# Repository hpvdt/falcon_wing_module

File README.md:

# falcon_wing_module
General purpose modules for handling wing duties

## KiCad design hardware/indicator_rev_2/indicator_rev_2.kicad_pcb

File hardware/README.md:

# Hardware Files

The designs for the wing module reside here. The module is an evolution of two separate boards on Falcon: the distributed voltage regulators (`servo_regulator`), and the spar load sensing boards (`spar_sensor`). As such, their design files are included in this repository for reference in addition to the actual wing module design files.

## Software Used

All designs were made in KiCad, version 9.0 as of writing.

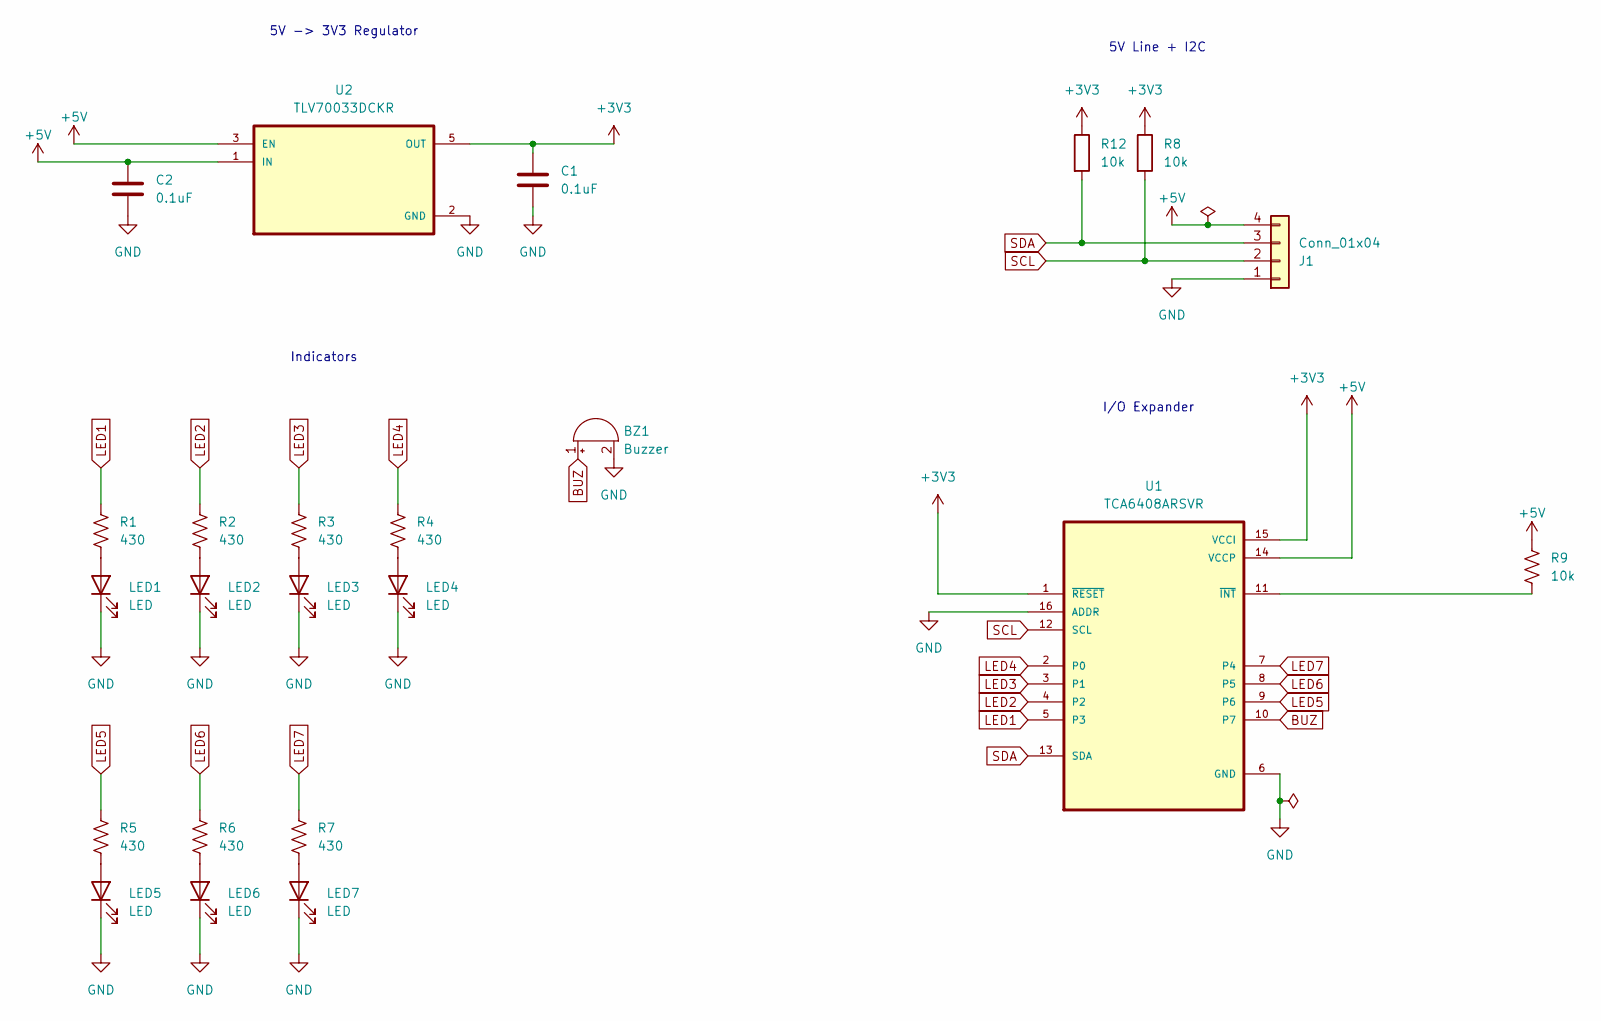
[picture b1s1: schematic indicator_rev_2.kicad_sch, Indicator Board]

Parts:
BZ1: Buzzer; Buzzer_12x9.5RM7.6
C1, C2: 0.1uF; C_0603_1608Metric
J1: Conn_01x04; JST_XH_S4B-XH-A_1x04_P2.50mm_Horizontal
LED1, LED2, LED3, LED4, LED5, LED6, LED7: LED; LED_D4.0mm
R1, R2, R3, R4, R5, R6, R7: 430; R_0603_1608Metric
R8, R9, R12: 10k; R_0603_1608Metric
U1: TCA6408ARSVR; QFN40P180X260X55-16N
U2: TLV70033DCKR; SOT65P210X110-5N

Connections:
+3V3: C1.1, R8.1, R12.1, U1.1 (~RESET), U1.15 (VCCI), U2.5 (OUT)
+5V: C2.1, J1.4, R9.2, U1.14 (VCCP), U2.1 (IN), U2.3 (EN)
BUZ: BZ1.1 (-), U1.10 (P7)
GND: BZ1.2 (+), C1.2, C2.2, J1.1, LED1.1 (K), LED2.1 (K), LED3.1 (K), LED4.1 (K), LED5.1 (K), LED6.1 (K), LED7.1 (K), U1.6 (GND), U1.16 (ADDR), U2.2 (GND)
LED1: R1.2, U1.5 (P3)
LED2: R2.2, U1.4 (P2)
LED3: R3.2, U1.3 (P1)
LED4: R4.2, U1.2 (P0)
LED5: R5.2, U1.9 (P6)
LED6: R6.2, U1.8 (P5)
LED7: R7.2, U1.7 (P4)
unnamed: LED1.2 (A), R1.1
unnamed: LED2.2 (A), R2.1
unnamed: LED3.2 (A), R3.1
unnamed: LED4.2 (A), R4.1
unnamed: LED5.2 (A), R5.1
unnamed: LED6.2 (A), R6.1
unnamed: LED7.2 (A), R7.1
unnamed: R9.1, U1.11 (~INT)
SCL: J1.2, R8.2, U1.12 (SCL)
SDA: J1.3, R12.2, U1.13 (SDA)

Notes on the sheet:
5V Line + I2C
I/O Expander
5V -> 3V3 Regulator
Indicators

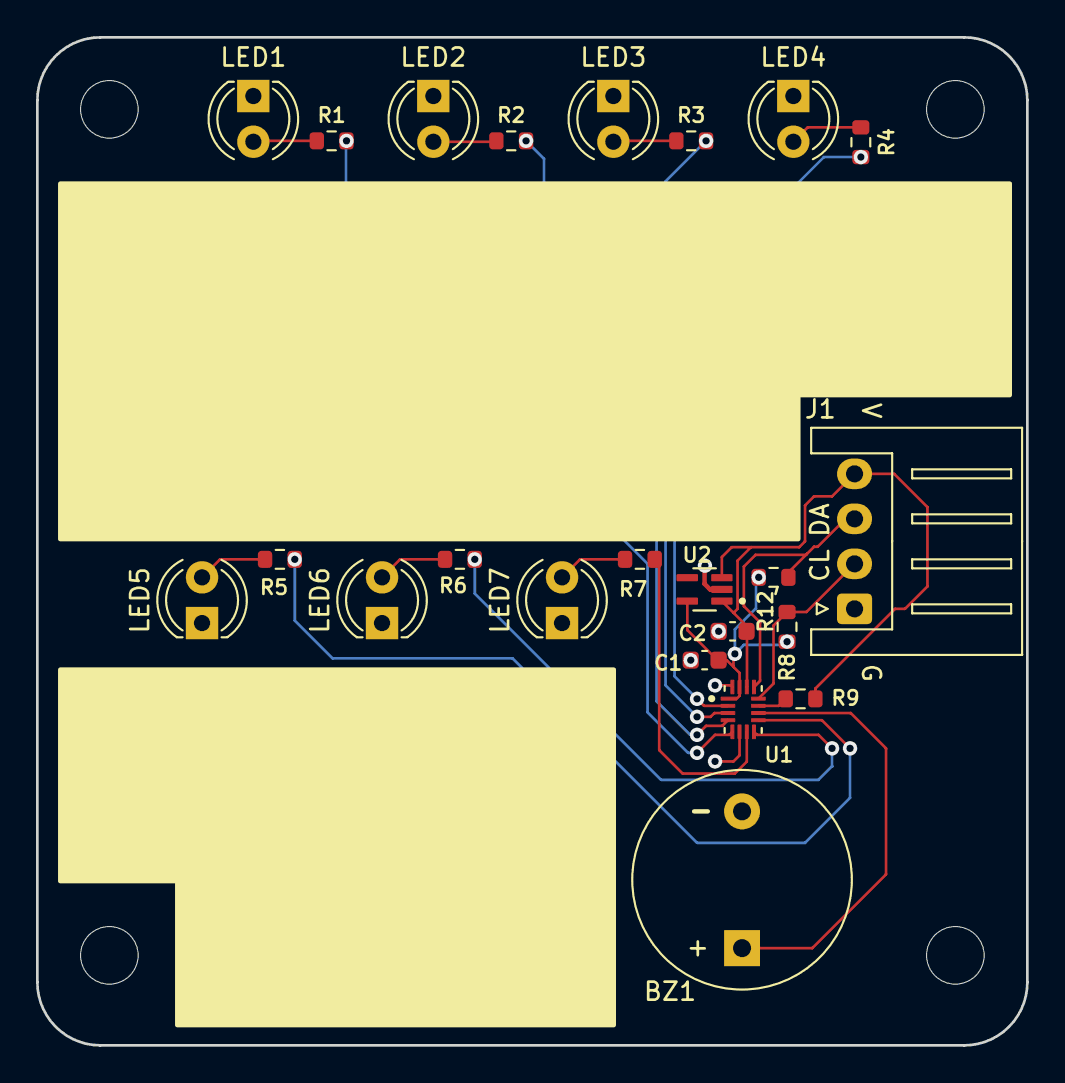
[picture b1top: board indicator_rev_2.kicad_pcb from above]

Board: 2 copper layers, 55.0 x 56.0 mm, 23 parts (0 on the bottom side), 21 nets.

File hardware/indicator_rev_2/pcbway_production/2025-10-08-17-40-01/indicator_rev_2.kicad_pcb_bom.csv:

Designator,Quantity,Value,Footprint,Package,MPN,DNP,Mount_Type,Description
BZ1,1,Buzzer,Buzzer_12x9.5RM7.6,"Plugin,D=12mm",KXG1203C,,tht,
"C1, C2",2,0.1uF,C_0603_1608Metric,0603,CL10B104KA8NNNC,,smt,Unpolarized capacitor
J1,1,Conn_01x04,JST_XH_S4B-XH-A_1x04_P2.50mm_Horizontal,"Push-Pull,P=2.5mm",S4B-XH-A(LF)(SN),,tht,"Generic connector, single row, 01x04, script generated (kicad-library-utils/schlib/autogen/connector/)"
"LED1, LED2, LED3, LED4, LED5, LED6, LED7",7,LED,LED_D4.0mm,"Plugin,D=4mm",TJ-L4FYTGCRMFCSFLC2R-A5,,tht,
"R1, R2, R3, R4, R5, R6, R7",7,430,R_0603_1608Metric,0603,0603WAF4300T5E,,smt,
"R12, R8, R9",3,10k,R_0603_1608Metric,0603,0603WAJ0103T5E,,smt,Resistor
U1,1,TCA6408ARSVR,QFN40P180X260X55-16N,UQFN-16(1.8x2.6),TCA6408ARSVR,,smt,
U2,1,TLV70033DCKR,SOT65P210X110-5N,SC-70-5,TLV70033DCKR,,smt,

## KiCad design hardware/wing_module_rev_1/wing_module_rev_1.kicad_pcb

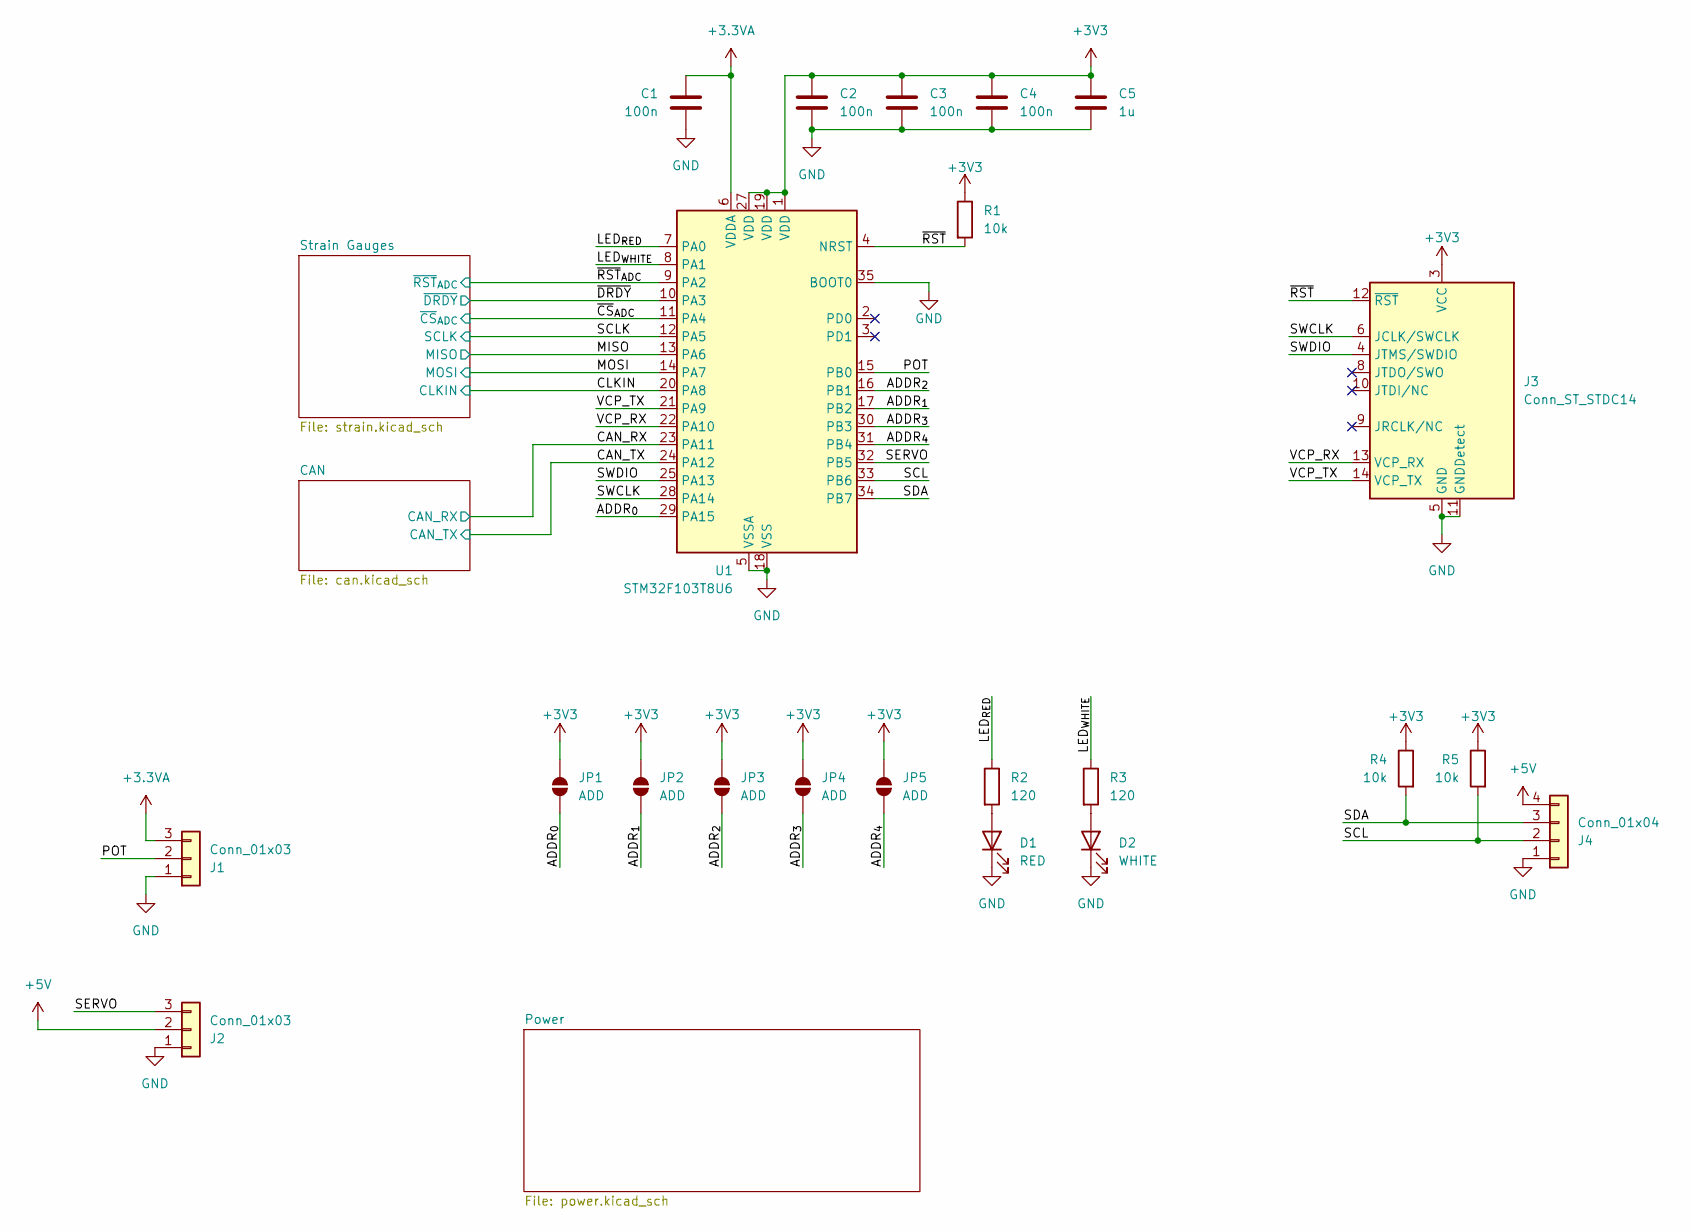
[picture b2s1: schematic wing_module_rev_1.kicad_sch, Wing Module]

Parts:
C1, C2, C3, C4: 100n; C_0402_1005Metric; LCSC C5448875
C5: 1u; C_0402_1005Metric; LCSC C52923
D1: RED; LED_0805_2012Metric; LCSC C84256
D2: WHITE; LED_0805_2012Metric; LCSC C34499
J1, J2: Conn_01x03; JST_EH_B3B-EH-A_1x03_P2.50mm_Vertical; LCSC C398546
J3: Conn_ST_STDC14; PinHeader_2x07_P1.27mm_Vertical_SMD; LCSC C6332251
J4: Conn_01x04; JST_EH_B4B-EH-A_1x04_P2.50mm_Vertical; LCSC C160258
JP1, JP2, JP3, JP4, JP5: ADD; SolderJumper-2_P1.3mm_Open_TrianglePad1.0x1.5mm; LCSC N/A
R1, R4, R5: 10k; R_0402_1005Metric; LCSC C723353
R2, R3: 120; R_0402_1005Metric; LCSC C25079
U1: STM32F103T8U6; QFN-36-1EP_6x6mm_P0.5mm_EP3.7x3.7mm; LCSC C19671

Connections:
+3.3VA: C1.1, J1.3, U1.6 (VDDA); also elsewhere on the board
+3V3: C2.1, C3.1, C4.1, C5.1, J3.3 (VCC), JP1.2 (B), JP2.2 (B), JP3.2 (B), JP4.2 (B), JP5.2 (B), R1.1, R4.1, R5.1, U1.1 (VDD), U1.19 (VDD), U1.27 (VDD); also elsewhere on the board
+5V: J2.2, J4.4; also elsewhere on the board
/ADDR_{0}: JP1.1 (A), U1.29 (PA15)
/ADDR_{1}: JP2.1 (A), U1.17 (PB2)
/ADDR_{2}: JP3.1 (A), U1.16 (PB1)
/ADDR_{3}: JP4.1 (A), U1.30 (PB3)
/ADDR_{4}: JP5.1 (A), U1.31 (PB4)
/CAN_RX: U1.23 (PA11); also elsewhere on the board
/CAN_TX: U1.24 (PA12); also elsewhere on the board
/CLKIN: U1.20 (PA8); also elsewhere on the board
/LED_{RED}: R2.1, U1.7 (PA0)
/LED_{WHITE}: R3.1, U1.8 (PA1)
/MISO: U1.13 (PA6); also elsewhere on the board
/MOSI: U1.14 (PA7); also elsewhere on the board
/POT: J1.2, U1.15 (PB0)
/SCL: J4.2, R5.2, U1.33 (PB6)
/SCLK: U1.12 (PA5); also elsewhere on the board
/SDA: J4.3, R4.2, U1.34 (PB7)
/SERVO: J2.3, U1.32 (PB5)
/SWCLK: J3.6 (JCLK/SWCLK), U1.28 (PA14)
/SWDIO: J3.4 (JTMS/SWDIO), U1.25 (PA13)
/VCP_RX: J3.13 (VCP_RX), U1.22 (PA10)
/VCP_TX: J3.14 (VCP_TX), U1.21 (PA9)
/~CS_{ADC}: U1.11 (PA4); also elsewhere on the board
/~DRDY: U1.10 (PA3); also elsewhere on the board
/~RST: J3.12 (~RST), R1.2, U1.4 (NRST)
/~RST_{ADC}: U1.9 (PA2); also elsewhere on the board
GND: C1.2, C2.2, C3.2, C4.2, C5.2, D1.1 (K), D2.1 (K), J1.1, J2.1, J3.5 (GND), J3.7 (GND), J3.11 (GNDDetect), J4.1, U1.5 (VSSA), U1.18 (VSS), U1.26 (VSS), U1.35 (BOOT0), U1.36 (VSS), U1.37 (VSS); also elsewhere on the board
unnamed: D1.2 (A), R2.2
unnamed: D2.2 (A), R3.2

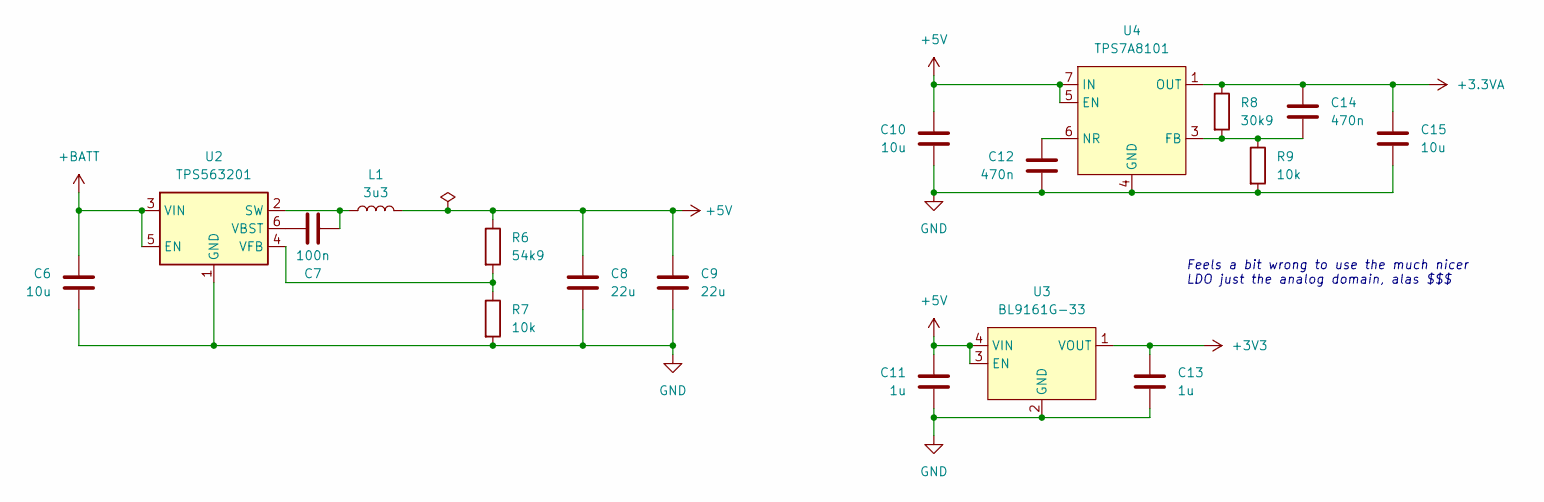
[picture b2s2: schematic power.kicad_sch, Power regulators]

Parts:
C6, C10, C15: 10u; C_0603_1608Metric; LCSC C5360828
C7: 100n; C_0402_1005Metric; LCSC C5448875
C8, C9: 22u; C_0603_1608Metric; LCSC C86295
C11, C13: 1u; C_0402_1005Metric; LCSC C52923
C12, C14: 470n; C_0402_1005Metric; LCSC C47339
L1: 3u3; L_Changjiang_FNR6045S; LCSC C168063
R6: 54k9; R_0402_1005Metric; LCSC C227137
R7, R9: 10k; R_0402_1005Metric; LCSC C723353
R8: 30k9; R_0402_1005Metric; LCSC C1883526
U2: TPS563201; SOT-23-6; LCSC C116592
U3: BL9161G-33; UDFN-4-1EP_1x1mm_P0.65mm_EP0.48x0.48mm; LCSC C2999146
U4: TPS7A8101; VSON-8-1EP_3x3mm_P0.65mm_EP1.65x2.4mm; LCSC C465730

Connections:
+3.3VA: C14.1, C15.1, R8.1, U4.1 (OUT), U4.2 (OUT); also elsewhere on the board
+3V3: C13.1, U3.1 (VOUT); also elsewhere on the board
+5V: C8.1, C9.1, C10.1, C11.1, L1.2, R6.1, U3.3 (EN), U3.4 (VIN), U4.5 (EN), U4.7 (IN), U4.8 (IN); also elsewhere on the board
+BATT: C6.1, U2.3 (VIN), U2.5 (EN); also elsewhere on the board
GND: C6.2, C8.2, C9.2, C10.2, C11.2, C12.2, C13.2, C15.2, R7.2, R9.2, U2.1 (GND), U3.2 (GND), U3.5 (GND), U4.4 (GND), U4.9 (GND); also elsewhere on the board
unnamed: C7.2, L1.1, U2.2 (SW)
unnamed: C7.1, U2.6 (VBST)
unnamed: R6.2, R7.1, U2.4 (VFB)
unnamed: C14.2, R8.2, R9.1, U4.3 (FB)
unnamed: C12.1, U4.6 (NR)

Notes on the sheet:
Feels a bit wrong to use the much nicer LDO just the analog domain, alas $$$

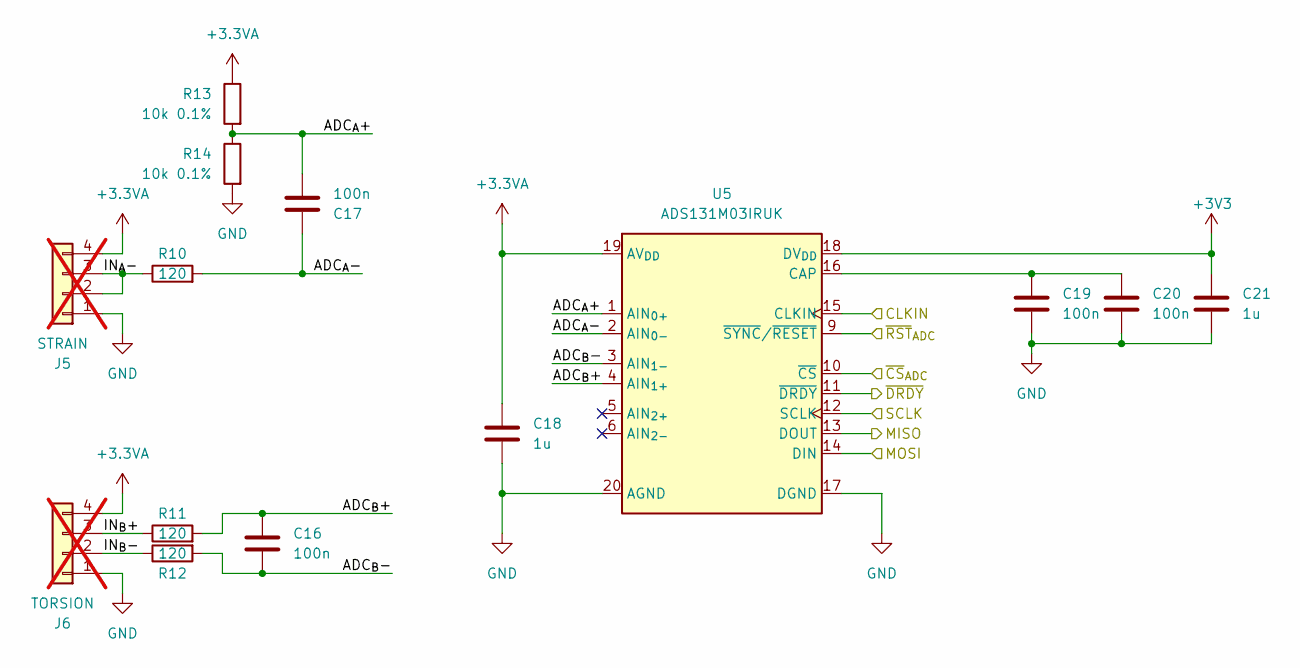
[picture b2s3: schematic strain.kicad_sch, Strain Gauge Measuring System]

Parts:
C16, C17, C19, C20: 100n; C_0402_1005Metric; LCSC C5448875
C18, C21: 1u; C_0402_1005Metric; LCSC C52923
J5: STRAIN; PinHeader_1x04_P2.00mm_Vertical; LCSC N/A; not fitted
J6: TORSION; PinHeader_1x04_P2.00mm_Vertical; LCSC N/A; not fitted
R10, R11, R12: 120; R_0402_1005Metric; LCSC C25079
R13, R14: 10k 0.1%; R_0402_1005Metric; LCSC C191915
U5: ADS131M03IRUK; WQFN-20-1EP_3x3mm_P0.4mm_EP1.7x1.7mm; LCSC C5116472

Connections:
+3.3VA: C18.1, J5.4, J6.4, R13.1, U5.19 (AV_{DD}); also elsewhere on the board
+3V3: C21.1, U5.18 (DV_{DD}); also elsewhere on the board
/CLKIN: U5.15 (CLKIN); also elsewhere on the board
/MISO: U5.13 (DOUT); also elsewhere on the board
/MOSI: U5.14 (DIN); also elsewhere on the board
/SCLK: U5.12 (SCLK); also elsewhere on the board
/Strain Gauges/ADC_{A}+: C17.2, R13.2, R14.1, U5.1 (AIN_{0+})
/Strain Gauges/ADC_{A}-: C17.1, R10.2, U5.2 (AIN_{0-})
/Strain Gauges/ADC_{B}+: C16.1, R11.2, U5.4 (AIN_{1+})
/Strain Gauges/ADC_{B}-: C16.2, R12.2, U5.3 (AIN_{1-})
/Strain Gauges/IN_{A}-: J5.2, J5.3, R10.1
/Strain Gauges/IN_{B}+: J6.3, R11.1
/Strain Gauges/IN_{B}-: J6.2, R12.1
/~CS_{ADC}: U5.10 (~CS); also elsewhere on the board
/~DRDY: U5.11 (~DRDY); also elsewhere on the board
/~RST_{ADC}: U5.9 (~SYNC/~RESET); also elsewhere on the board
GND: C18.2, C19.2, C20.2, C21.2, J5.1, J6.1, R14.2, U5.17 (DGND), U5.20 (AGND), U5.21 (AGND); also elsewhere on the board
unnamed: C19.1, C20.1, U5.16 (CAP)

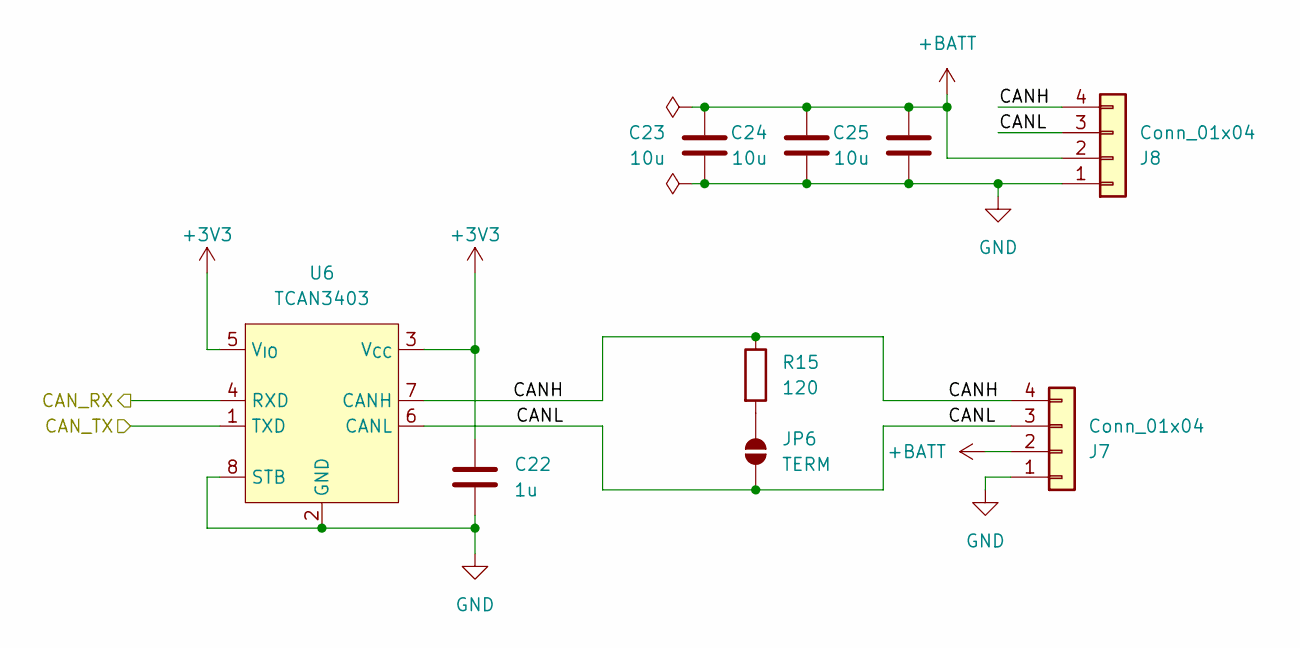
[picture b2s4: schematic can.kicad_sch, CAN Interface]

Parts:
C22: 1u; C_0402_1005Metric; LCSC C52923
C23, C24, C25: 10u; C_0603_1608Metric; LCSC C5360828
J7, J8: Conn_01x04; JST_EH_B4B-EH-A_1x04_P2.50mm_Vertical; LCSC C160258
JP6: TERM; SolderJumper-2_P1.3mm_Open_TrianglePad1.0x1.5mm; LCSC N/A
R15: 120; R_0402_1005Metric; LCSC C25079
U6: TCAN3403; TSOT-23-8; LCSC C35926232

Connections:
+3V3: C22.1, U6.3 (V_{CC}), U6.5 (V_{IO}); also elsewhere on the board
+BATT: C23.1, C24.1, C25.1, J7.2, J8.2; also elsewhere on the board
/CAN/CANH: J7.4, J8.4, R15.1, U6.7 (CANH)
/CAN/CANL: J7.3, J8.3, JP6.2 (B), U6.6 (CANL)
/CAN_RX: U6.4 (RXD); also elsewhere on the board
/CAN_TX: U6.1 (TXD); also elsewhere on the board
GND: C22.2, C23.2, C24.2, C25.2, J7.1, J8.1, U6.2 (GND), U6.8 (STB); also elsewhere on the board
unnamed: JP6.1 (A), R15.2

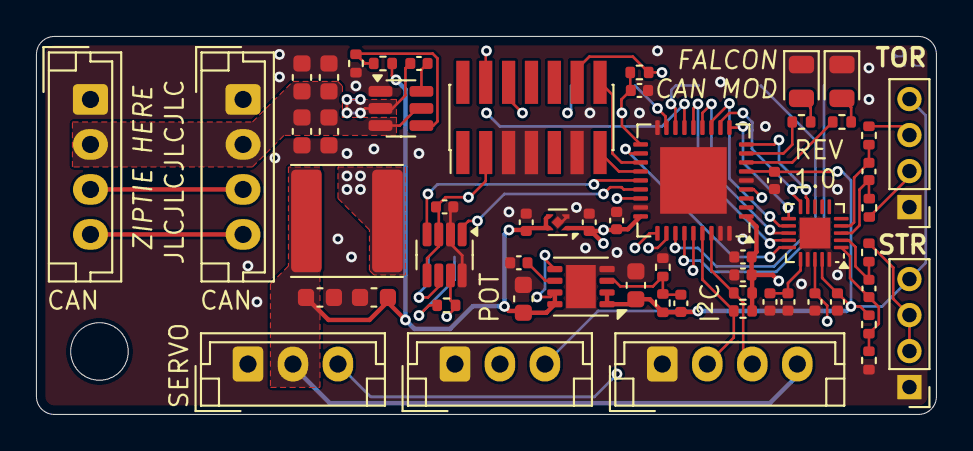
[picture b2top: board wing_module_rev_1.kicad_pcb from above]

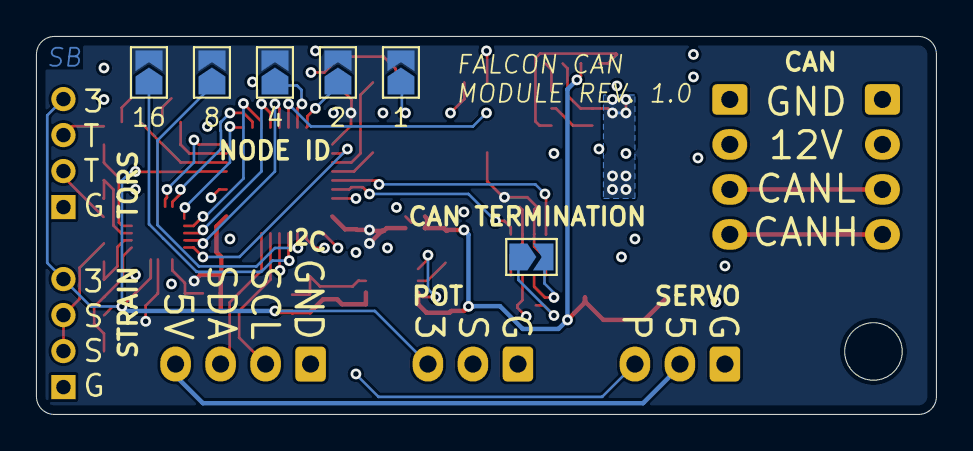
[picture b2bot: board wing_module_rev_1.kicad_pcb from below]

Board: 4 copper layers, 50.0 x 21.0 mm, 63 parts (6 on the bottom side), 48 nets.

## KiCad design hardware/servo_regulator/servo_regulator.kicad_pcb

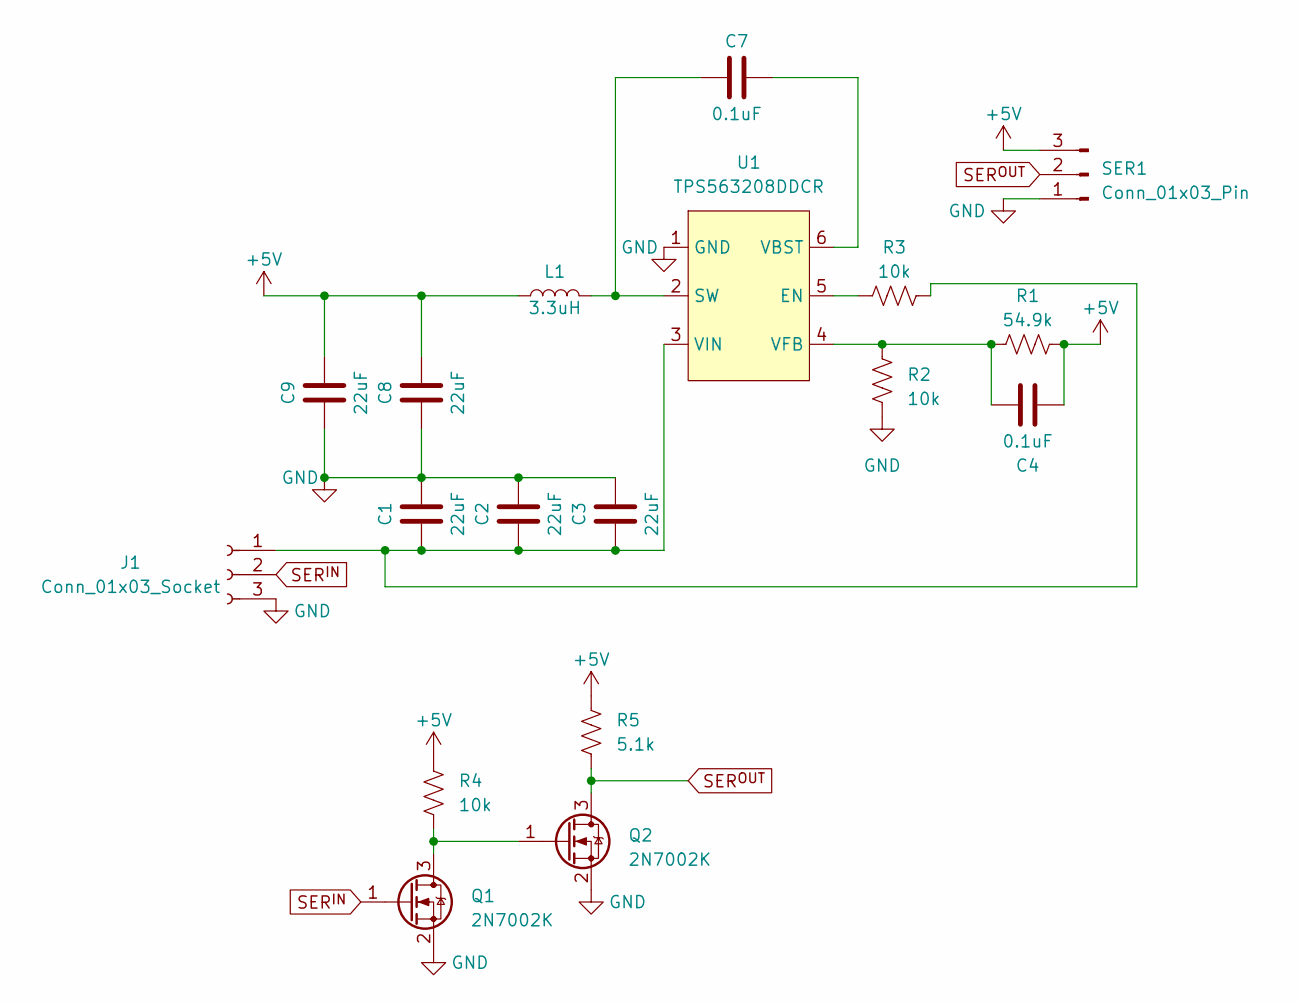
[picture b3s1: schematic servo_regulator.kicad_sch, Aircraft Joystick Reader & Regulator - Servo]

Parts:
C1, C2, C3, C8, C9: 22uF; C_0805_2012Metric
C4, C7: 0.1uF; C_0805_2012Metric
J1: Conn_01x03_Socket; JST_EH_B3B-EH-A_1x03_P2.50mm_Vertical
L1: 3.3uH; L_Taiyo-Yuden_NR-60xx
Q1, Q2: 2N7002K; SOT-23
R1: 54.9k; R_0603_1608Metric
R2, R3, R4: 10k; R_0603_1608Metric
R5: 5.1k; R_0603_1608Metric
SER1: Conn_01x03_Pin; JST_EH_B3B-EH-A_1x03_P2.50mm_Vertical
U1: TPS563208DDCR; TSOT-23-6

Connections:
+5V: C4.2, C8.2, C9.2, L1.1, R1.1, R4.1, R5.1, SER1.3
GND: C1.2, C2.2, C3.2, C8.1, C9.1, J1.3, Q1.2 (S), Q2.2 (S), R2.1, SER1.1, U1.1 (GND)
unnamed: C1.1, C2.1, C3.1, J1.1, R3.2, U1.3 (VIN)
unnamed: Q1.3 (D), Q2.1 (G), R4.2
unnamed: R3.1, U1.5 (EN)
unnamed: C7.1, L1.2, U1.2 (SW)
unnamed: C7.2, U1.6 (VBST)
unnamed: C4.1, R1.2, R2.2, U1.4 (VFB)
SER^{IN}: J1.2, Q1.1 (G)
SER^{OUT}: Q2.3 (D), R5.2, SER1.2

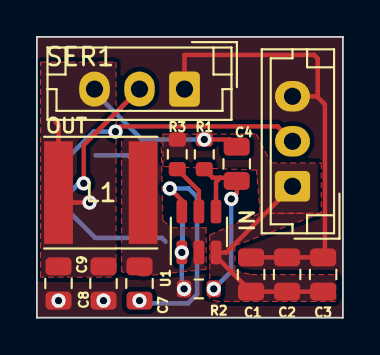
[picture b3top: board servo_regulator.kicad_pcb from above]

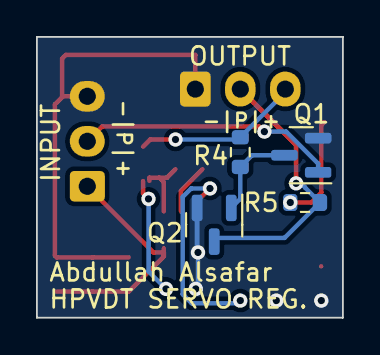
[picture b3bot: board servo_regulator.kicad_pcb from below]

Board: 2 copper layers, 17.0 x 15.6 mm, 18 parts (4 on the bottom side), 10 nets.

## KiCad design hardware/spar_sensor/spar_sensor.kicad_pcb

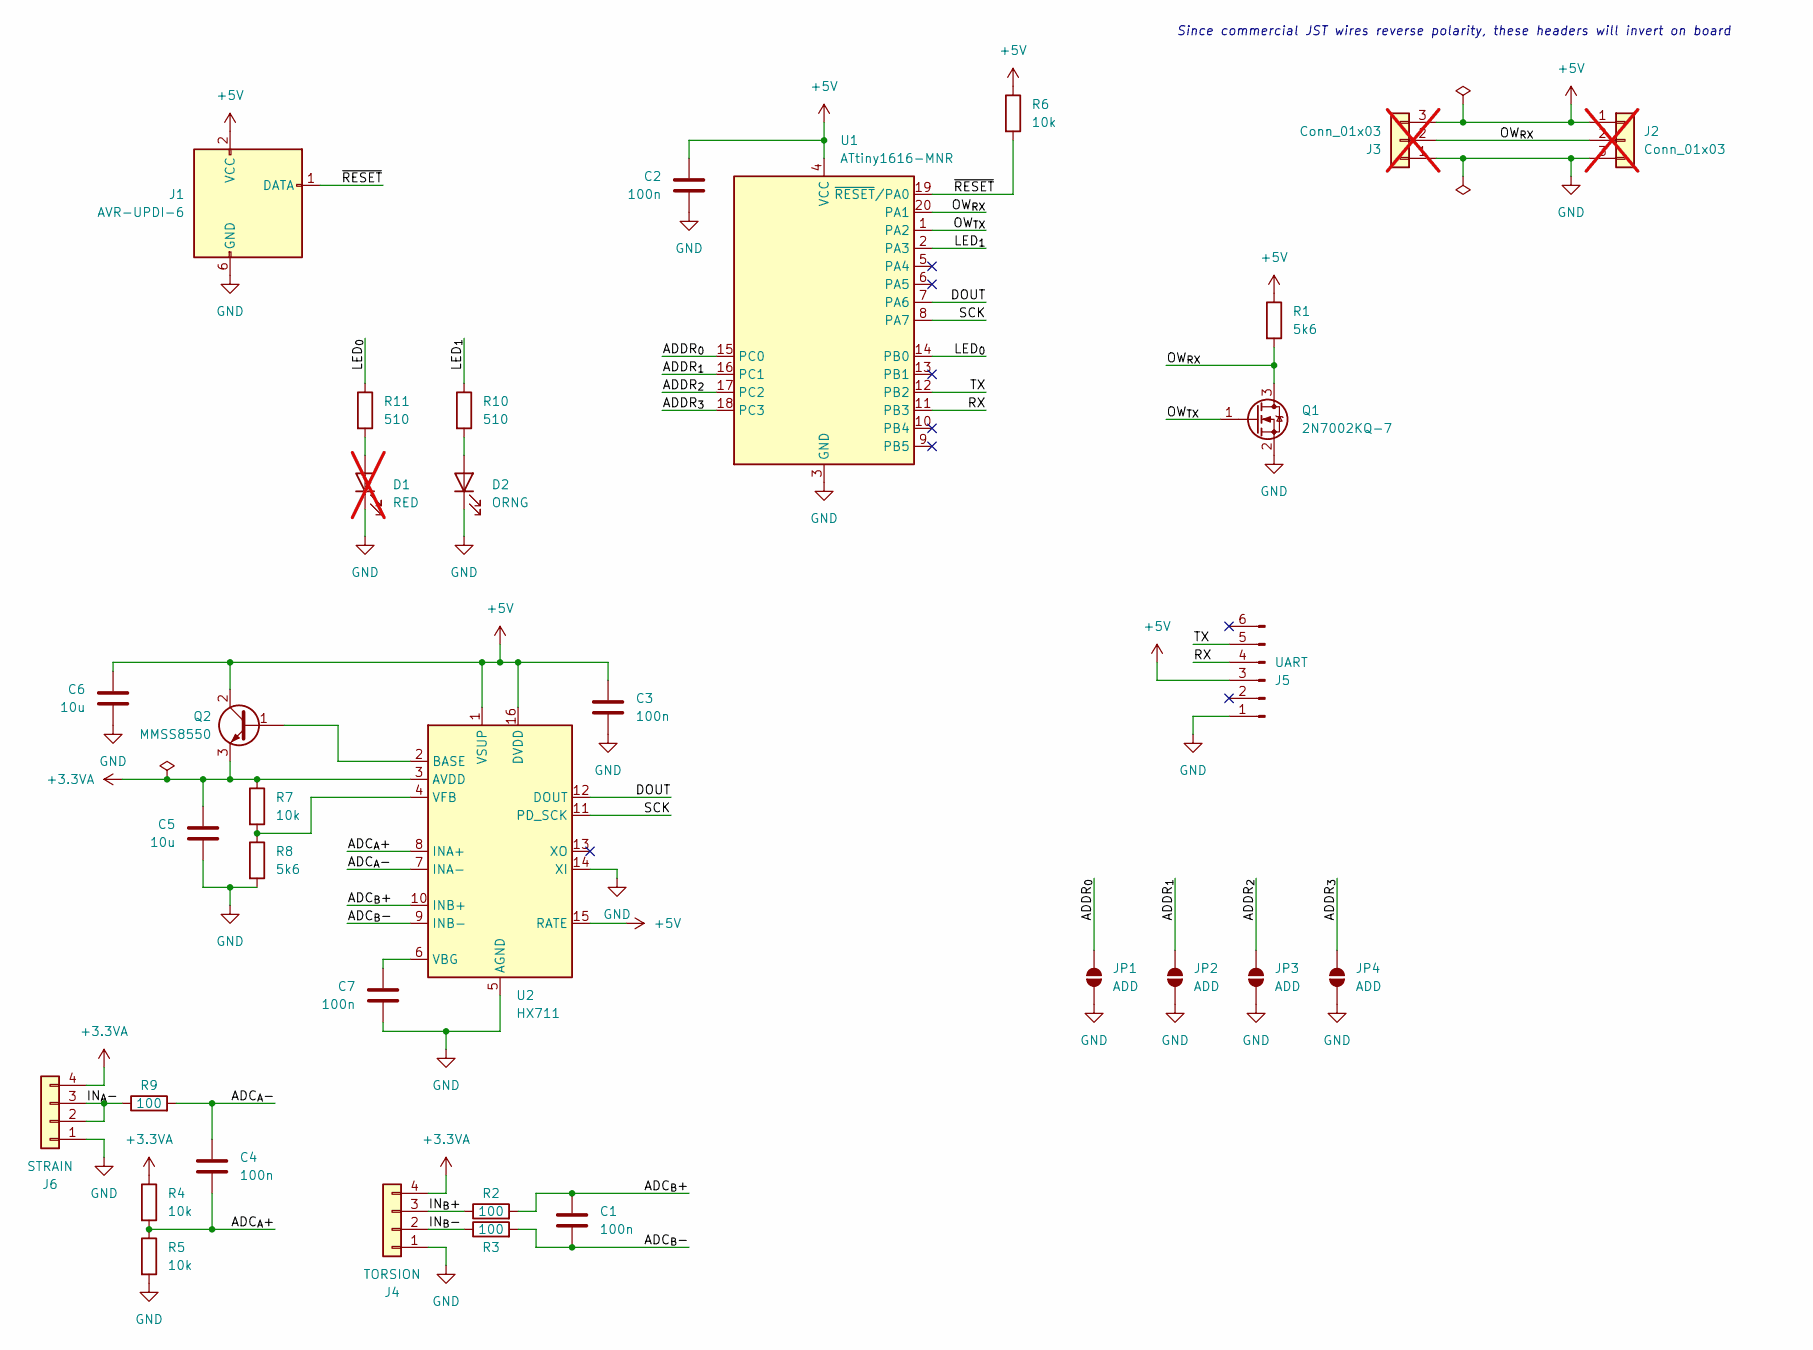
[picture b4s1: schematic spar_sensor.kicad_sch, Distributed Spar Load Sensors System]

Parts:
C1, C2, C3, C4, C7: 100n; C_0402_1005Metric; LCSC C5448875
C5, C6: 10u; C_0603_1608Metric; LCSC C5360828
D1: RED; LED_0805_2012Metric; LCSC N/A; not fitted
D2: ORNG; LED_0805_2012Metric; LCSC C2292
J1: AVR-UPDI-6; Tag-Connect_TC2030-IDC-NL_2x03_P1.27mm_Vertical; LCSC N/A
J2, J3: Conn_01x03; JST_EH_B3B-EH-A_1x03_P2.50mm_Vertical; LCSC C398546; not fitted
J4: TORSION; PinHeader_1x04_P2.00mm_Vertical; LCSC N/A
J5: UART; PinHeader_1x06_P2.54mm_Vertical; LCSC N/A
J6: STRAIN; PinHeader_1x04_P2.00mm_Vertical; LCSC N/A
JP1, JP2, JP3, JP4: ADD; SolderJumper-2_P1.3mm_Open_TrianglePad1.0x1.5mm; LCSC N/A
Q1: 2N7002KQ-7; SOT-23; LCSC C111971
Q2: MMSS8550; SOT-23; LCSC C192429
R1, R8: 5k6; R_0402_1005Metric; LCSC C340537
R2, R3, R9: 100; R_0402_1005Metric; LCSC C606168
R4, R5: 10k; R_0402_1005Metric; LCSC C191915
R6, R7: 10k; R_0402_1005Metric; LCSC C723353
R10, R11: 510; R_0402_1005Metric; LCSC C2991609
U1: ATtiny1616-MNR; VQFN-20-1EP_3x3mm_P0.4mm_EP1.7x1.7mm; LCSC C507118
U2: HX711; SOP-16_3.9x9.9mm_P1.27mm; LCSC C6705483

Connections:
+3.3VA: C5.1, J4.4, J6.4, Q2.3 (E), R4.1, R7.1, U2.3 (AVDD)
+5V: C2.1, C3.1, C6.1, J1.2 (VCC), J2.1, J3.3, J5.3, Q2.2 (C), R1.1, R6.1, U1.4 (VCC), U2.1 (VSUP), U2.15 (RATE), U2.16 (DVDD)
/ADC_{A}+: C4.2, R4.2, R5.1, U2.8 (INA+)
/ADC_{A}-: C4.1, R9.2, U2.7 (INA-)
/ADC_{B}+: C1.1, R2.2, U2.10 (INB+)
/ADC_{B}-: C1.2, R3.2, U2.9 (INB-)
/ADDR_{0}: JP1.2 (B), U1.15 (PC0)
/ADDR_{1}: JP2.2 (B), U1.16 (PC1)
/ADDR_{2}: JP3.2 (B), U1.17 (PC2)
/ADDR_{3}: JP4.2 (B), U1.18 (PC3)
/DOUT: U1.7 (PA6), U2.12 (DOUT)
/IN_{A}-: J6.2, J6.3, R9.1
/IN_{B}+: J4.3, R2.1
/IN_{B}-: J4.2, R3.1
/LED_{0}: R11.1, U1.14 (PB0)
/LED_{1}: R10.1, U1.2 (PA3)
/OW_{RX}: J2.2, J3.2, Q1.3 (D), R1.2, U1.20 (PA1)
/OW_{TX}: Q1.1 (G), U1.1 (PA2)
/RX: J5.4, U1.11 (PB3)
/SCK: U1.8 (PA7), U2.11 (PD_SCK)
/TX: J5.5, U1.12 (PB2)
/~RESET: J1.1 (DATA), R6.2, U1.19 (~RESET/PA0)
GND: C2.2, C3.2, C5.2, C6.2, C7.2, D1.1 (K), D2.1 (K), J1.6 (GND), J2.3, J3.1, J4.1, J5.1, J6.1, JP1.1 (A), JP2.1 (A), JP3.1 (A), JP4.1 (A), Q1.2 (S), R5.2, R8.2, U1.3 (GND), U1.21 (GND), U2.5 (AGND), U2.14 (XI)
unnamed: D1.2 (A), R11.2
unnamed: D2.2 (A), R10.2
unnamed: Q2.1 (B), U2.2 (BASE)
unnamed: C7.1, U2.6 (VBG)
unnamed: R7.2, R8.1, U2.4 (VFB)

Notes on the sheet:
Since commercial JST wires reverse polarity, these headers will invert on board

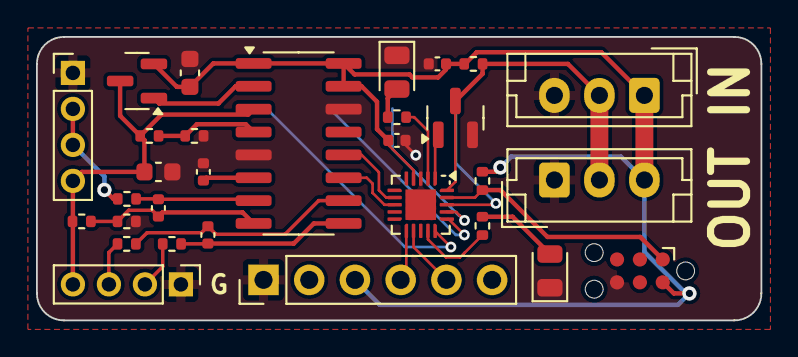
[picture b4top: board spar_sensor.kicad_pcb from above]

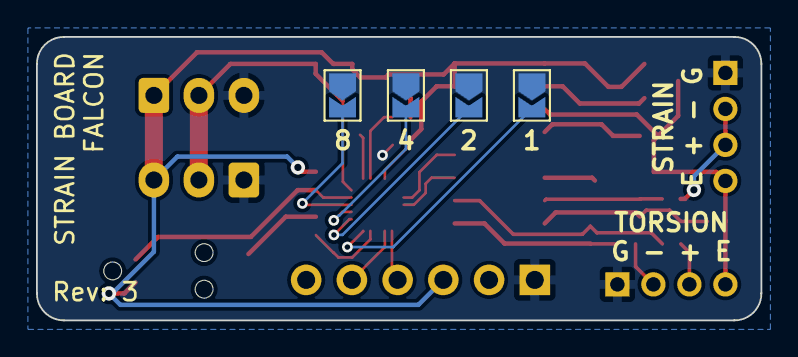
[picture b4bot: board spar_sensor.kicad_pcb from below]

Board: 2 copper layers, 40.2 x 15.8 mm, 34 parts (4 on the bottom side), 28 nets.

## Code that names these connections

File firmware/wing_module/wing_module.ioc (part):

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Mcu.Name=STM32F103T(8-B)Ux
Mcu.Package=VFQFPN36
Mcu.UserName=STM32F103T8Ux
PA0-WKUP.GPIOParameters=GPIO_Speed,GPIO_Label
PA0-WKUP.GPIO_Label=LED_RED
PA0-WKUP.GPIO_Speed=GPIO_SPEED_FREQ_LOW
PA0-WKUP.Signal=S_TIM2_CH1_ETR
PA1.GPIOParameters=GPIO_Label
PA1.GPIO_Label=LED_WHITE
PA1.Signal=S_TIM2_CH2
PA10.Mode=Asynchronous
PA10.Signal=USART1_RX
PA11.Mode=CAN_Activate
PA11.Signal=CAN_RX
PA12.Mode=CAN_Activate
PA12.Signal=CAN_TX
PA13.Mode=Serial_Wire
PA13.Signal=SYS_JTMS-SWDIO
PA14.Mode=Serial_Wire
PA14.Signal=SYS_JTCK-SWCLK
PA15.GPIOParameters=GPIO_PuPd,GPIO_Label
PA15.GPIO_Label=ADDR_0
PA15.GPIO_PuPd=GPIO_PULLDOWN
PA15.Signal=GPIO_Input
PA2.GPIOParameters=GPIO_Label
PA2.GPIO_Label=ADS_RESET
PA2.Signal=GPIO_Output
PA3.GPIOParameters=GPIO_PuPd,GPIO_Label
PA3.GPIO_Label=ADS_DATA_RDY
PA3.GPIO_PuPd=GPIO_PULLUP
PA3.Signal=GPIO_Input
PA4.GPIOParameters=GPIO_Label
PA4.GPIO_Label=ADS_CS
PA4.Signal=GPIO_Output
PA5.Mode=Full_Duplex_Master
PA5.Signal=SPI1_SCK
PA6.Mode=Full_Duplex_Master
PA6.Signal=SPI1_MISO
PA7.Mode=Full_Duplex_Master
PA7.Signal=SPI1_MOSI
PA8.GPIOParameters=GPIO_Label
PA8.GPIO_Label=ADC_CLK_IN
PA8.Mode=Clock-out
PA8.Signal=RCC_MCO
PA9.Mode=Asynchronous
PA9.Signal=USART1_TX
PB0.GPIOParameters=GPIO_Label
PB0.GPIO_Label=ANG_POT
PB0.Signal=ADCx_IN8
PB1.GPIOParameters=GPIO_PuPd,GPIO_Label
PB1.GPIO_Label=ADDR_2
PB1.GPIO_PuPd=GPIO_PULLDOWN
PB1.Signal=GPIO_Input
PB2.GPIOParameters=GPIO_PuPd,GPIO_Label
PB2.GPIO_Label=ADDR_1
PB2.GPIO_PuPd=GPIO_PULLDOWN
PB2.Signal=GPIO_Input
PB3.GPIOParameters=GPIO_PuPd,GPIO_Label
PB3.GPIO_Label=ADDR_3
PB3.GPIO_PuPd=GPIO_PULLDOWN
PB3.Signal=GPIO_Input
PB4.GPIOParameters=GPIO_PuPd,GPIO_Label
PB4.GPIO_Label=ADDR_4
PB4.GPIO_PuPd=GPIO_PULLDOWN
PB4.Signal=GPIO_Input
PB5.GPIOParameters=GPIO_Label
PB5.GPIO_Label=SERVO_PWM
PB5.Signal=S_TIM3_CH2
PB6.Signal=I2C1_SCL
PB7.Signal=I2C1_SDA
RCC.SYSCLKFreq_VALUE=64000000
RCC.SYSCLKSource=RCC_SYSCLKSOURCE_PLLCLK
board=custom

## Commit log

2025-08-09 Uploaded original hardware designs
2025-08-09 Added firmware for previous spar sensor
2025-08-14 Completed schematic for rev 1
2025-08-14 Drafted configuration for rev 1
2025-08-14 Split up schematic into multple pages, added CS pullup for ADC
2025-08-15 FIxed missing ADC heirarchical labels
2025-08-16 Adjusted CAN connector order, drafting floorplan
2025-08-17 Finished rev 1.0 layout of CAN
2025-08-17 Reassigned reference numbers
2025-08-17 Adjusted node address pins based on layout
2025-08-17 Added JLC tracking marker
2025-08-17 created indicator file
2025-08-17 added indicator board files
2025-08-18 Moved project for indicator board and updated the library symbols
2025-08-29 Inital draft of CAN code
2025-08-30 Initial draft of basic ADS131M03 driver
2025-08-30 Added code to average and calculate strain loading
2025-08-30 Fixed broadcast base IDs
2025-08-30 Adjusting behaviour do more precisely require configurations
2025-08-31 LED control drafted
2025-08-31 Start PWM outputs on boot
2025-08-31 Fixed LED control logic for pulses
2025-08-31 Added `printf()` to UART code
2025-08-31 Updated ADC config and added calibration
2025-08-31 Drafted control surface code
2025-09-01 Added diagrams of wing atuation mechanism
2025-09-02 Added angle alarm disabling
2025-09-02 Prepared CAN wrapper code for proper packing/unpacking of messages
2025-09-02 Added script for calculating wing sweep
2025-09-03 fixed mounting holes and connector
2025-09-03 updated mounting holes and connector
2025-09-03 Fixed LED variable sizing and constants
2025-09-03 Updated default PWM parameters
2025-09-03 Fixed integer division so result is signed
2025-09-03 Fixed `printf()` string terminations to \r\n
2025-09-03 Updated launch configurations
2025-09-03 Changed ADC reading to be signed for proper operation
2025-09-04 Made servo contol loop polled
2025-09-04 Adjusted servo PWM parameters to 50 Hz
2025-09-04 Disabled I2C due to conflict with servo PWM
2025-09-04 Adjusted CAN to 1Mb/s
2025-09-04 CAN bit timing tweak
2025-09-07 modified i2c header and pushed connector
2025-09-11 added b. silkscreen text & modified board colours
2025-09-11 added b.silkscreen text and changed board colours
2025-09-16 Changed CAN to 500 kB/s
2025-09-16 Fiixed some header defines
2025-09-16 Added CAN start/stops when changing filters
2025-09-16 Added function to block on CAN sending
2025-09-16 Fixed some bit-fielded enums to structs
2025-09-16 Fixed CAN data marshalling and buffer prep
2025-09-16 Fixed CAN filter updating to be done whenever needed
2025-09-16 Removed servo testing code
2025-10-08 added production files
2025-10-26 Fixed ANGLE command filter assignment
